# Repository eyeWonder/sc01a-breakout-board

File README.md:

# sc01a-breakout-board
An easy way to interface and play with the SC01A Voice Synthisizer

This chip has a really nostalgic sound in its robotic voice. Can't wait to hook this up to my OP-1!

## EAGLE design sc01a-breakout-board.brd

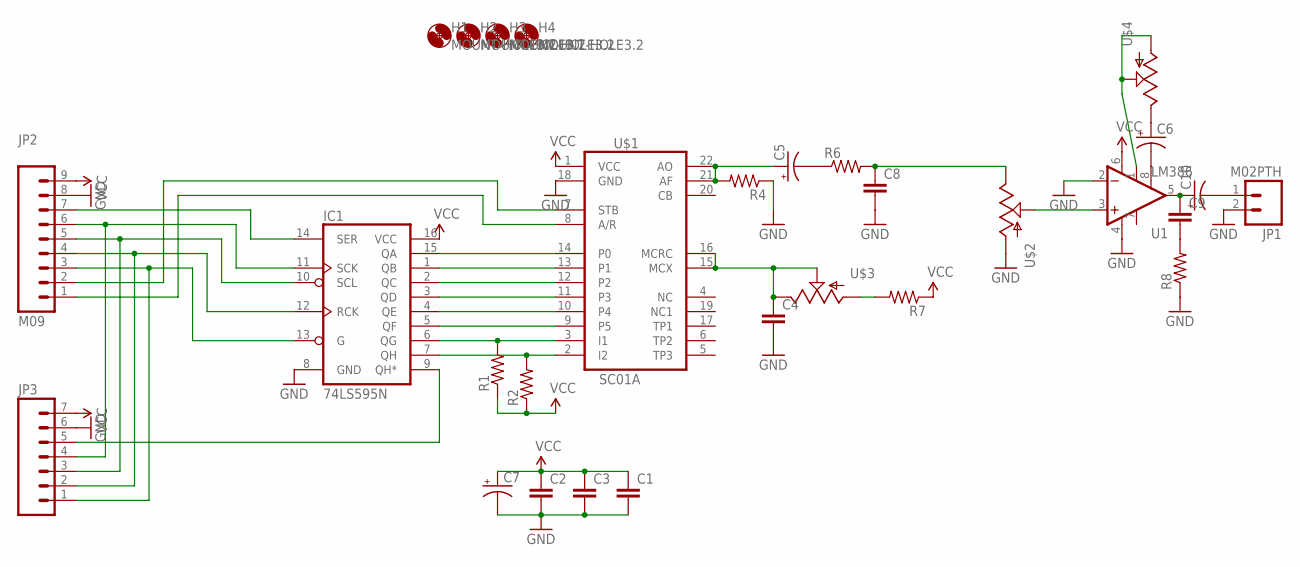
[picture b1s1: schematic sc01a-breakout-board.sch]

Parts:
C1, C2, C3, C4, C8, C9: CAPEZ; CAP-PTH-SMALLEZ
C5, C6, C7, C10: CAP_POLPTH2; CPOL-RADIAL-10UF-25V
H1, H2, H3, H4: MOUNT-HOLE3.2; 3,2
IC1: 74LS595N; DIL16
JP1: M02PTH; 1X02
JP2: M09; 1X09
JP3: M07; 1X07
R1, R2, R4, R6, R7, R8: R-US_0204/5; 0204/5
U1: LM386; DIP08
U$1: SC01A; 22PDIP4
U$2, U$3, U$4: POTTRIM; TRIM_POT

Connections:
GND: C1.2, C2.2, C3.2, C4.2, C7.2 (-), C8.2, IC1.8 (GND), JP1.2, JP2.8, JP3.6, R4.1, R8.1, U1.2 (-IN), U1.4 (V-), U$1.18 (GND), U$2.3 (A)
unnamed: IC1.1 (QB), U$1.13 (P1)
unnamed: IC1.2 (QC), U$1.12 (P2)
unnamed: IC1.3 (QD), U$1.11 (P3)
unnamed: IC1.4 (QE), U$1.10 (P4)
unnamed: IC1.5 (QF), U$1.9 (P5)
unnamed: IC1.6 (QG), R1.2, U$1.3 (I1)
unnamed: IC1.7 (QH), R2.2, U$1.2 (I2)
unnamed: IC1.15 (QA), U$1.14 (P0)
unnamed: C5.1 (+), R4.2, U$1.21 (AF), U$1.22 (AO)
unnamed: C5.2 (-), R6.1
unnamed: C8.1, R6.2, U$2.2 (E)
unnamed: C4.1, U$1.15 (MCX), U$1.16 (MCRC), U$3.1 (S), U$3.2 (E)
unnamed: R7.2, U$3.3 (A)
unnamed: JP2.2, U$1.7 (STB)
unnamed: JP2.1, U$1.8 (A/R)
unnamed: IC1.9 (QH*), JP3.5
unnamed: IC1.14 (SER), JP2.7
unnamed: U1.3 (+IN), U$2.1 (S)
unnamed: C6.2 (-), U1.8 (GAIN)
unnamed: C6.1 (+), U$4.2 (E)
unnamed: U1.1 (GAIN), U$4.1 (S), U$4.3 (A)
unnamed: C9.1, C10.1 (+), U1.5 (OUT)
unnamed: C9.2, R8.2
unnamed: C10.2 (-), JP1.1
unnamed: IC1.11 (SCK), JP2.6, JP3.4
unnamed: IC1.10 (SCL), JP2.5, JP3.3
unnamed: IC1.12 (RCK), JP2.4, JP3.2
unnamed: IC1.13 (G), JP2.3, JP3.1
VCC: C1.1, C2.1, C3.1, C7.1 (+), IC1.16 (VCC), JP2.9, JP3.7, R1.1, R2.1, R7.1, U1.6 (V+), U$1.1 (VCC)

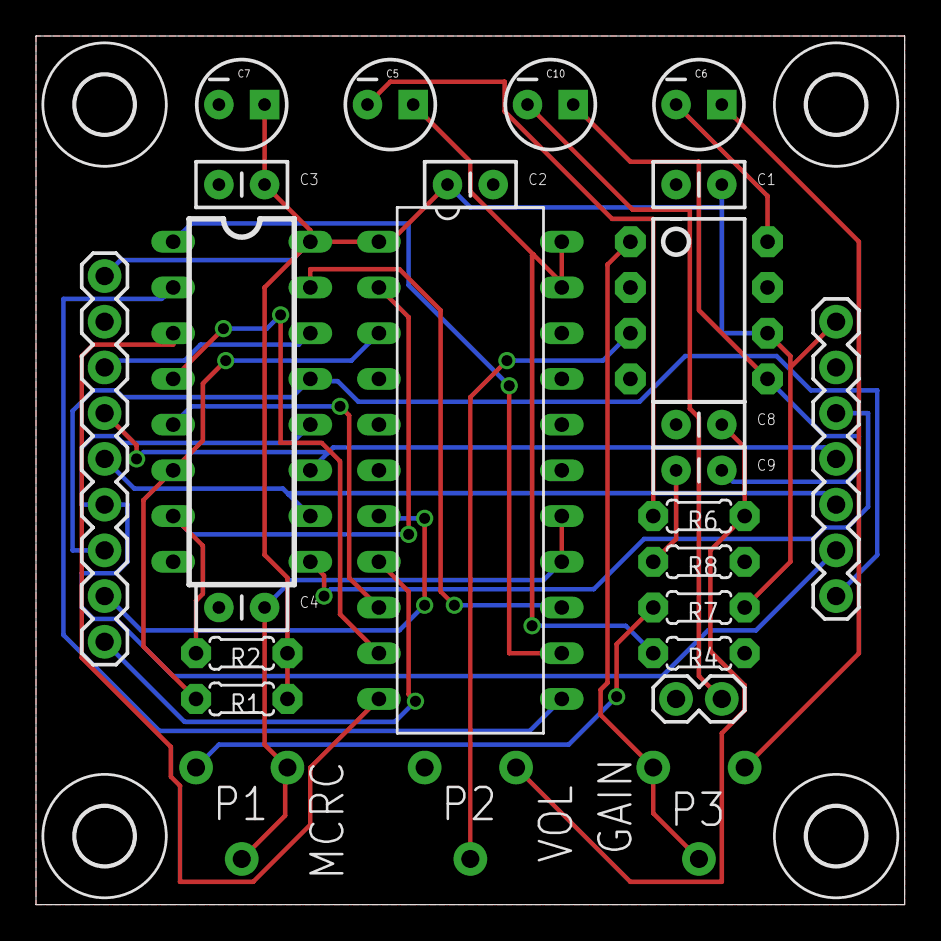
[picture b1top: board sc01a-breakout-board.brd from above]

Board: 2 copper layers, 48.3 x 48.3 mm, 29 parts (0 on the bottom side), 30 nets.

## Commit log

2018-07-05 design tested: working

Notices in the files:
parts and their libraries:
SparkFun-AnalogIC: Licensing: CC v3.0 Share-Alike You are welcome to use this library for commercial purposes.
